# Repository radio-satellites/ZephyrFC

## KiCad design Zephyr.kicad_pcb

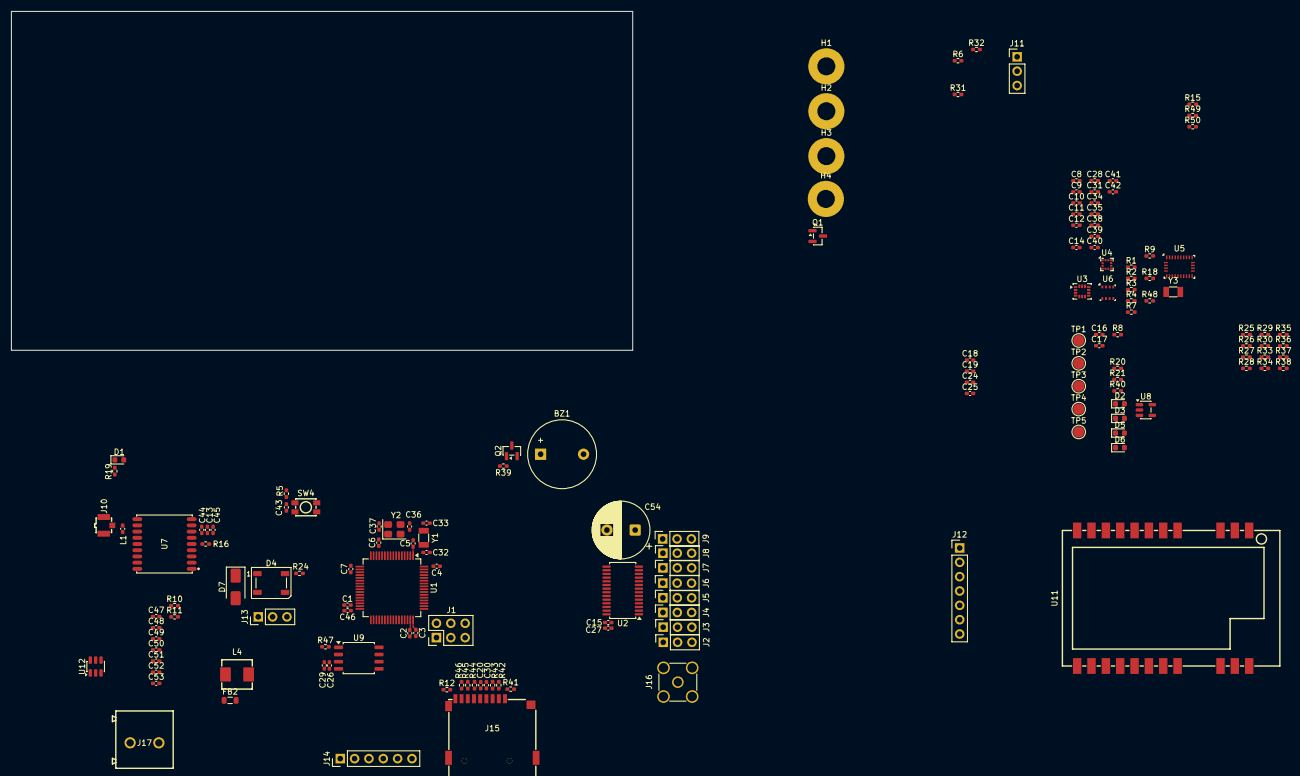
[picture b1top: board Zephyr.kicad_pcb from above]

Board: 2 copper layers, 110.0 x 60.0 mm, 150 parts (0 on the bottom side), 94 nets.

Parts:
BZ1: Buzzer; Buzzer_12x9.5RM7.6
C1, C2, C24, C27, C28, C30, C35, C39, C42, C45, C47: 10uF; C_0402_1005Metric_Pad0.74x0.62mm_HandSolder
C3, C4, C5, C6, C7, C12, C13, C14, C15, C19, C20, C25, C26, C31, C34, C38, C40, C41, C43, C44, C46, C48, C49: 100nF; C_0402_1005Metric_Pad0.74x0.62mm_HandSolder
C8, C9: 18pF; C_0402_1005Metric_Pad0.74x0.62mm_HandSolder
C10, C11, C18, C29: 1uF; C_0402_1005Metric_Pad0.74x0.62mm_HandSolder
C16, C17: 22uF; C_0402_1005Metric_Pad0.74x0.62mm_HandSolder
C32, C33: 15pF; C_0402_1005Metric_Pad0.74x0.62mm_HandSolder
C36, C37: 14pF; C_0402_1005Metric_Pad0.74x0.62mm_HandSolder
C50, C51: 47uF; C_0402_1005Metric_Pad0.74x0.62mm_HandSolder
C52: 75pF; C_0402_1005Metric_Pad0.74x0.62mm_HandSolder
C53: 1nF; C_0402_1005Metric_Pad0.74x0.62mm_HandSolder
C54: 470uF; CP_Radial_D10.0mm_P5.00mm
D1, D2, D3, D5, D6: LED; LED_0603_1608Metric
D4: WS2812B-B/T; LED_WS2812B_PLCC4_5.0x5.0mm_P3.2mm
D7: SS14; D_SMA
FB2: FerriteBead; L_0805_2012Metric
H1, H2, H3, H4: MountingHole_Pad; MountingHole_3.2mm_M3_Pad
J1: Conn_02x03_Counter_Clockwise; PinHeader_2x03_P2.54mm_Vertical
J2, J3, J4, J5, J6, J7, J8, J9: Conn_01x03; PinSocket_1x03_P2.54mm_Vertical
J10: Conn_Coaxial; RF-SMD_FRF05002-JSS103M
J11, J13: Conn_01x03; PinHeader_1x03_P2.54mm_Vertical
J12: Conn_01x07_Pin; PinHeader_1x07_P2.54mm_Vertical
J14: Conn_01x06; PinHeader_1x06_P2.54mm_Vertical
J15: Micro_SD_Card; TF-SMD_HX-TF-CARD-H1.8-SY
J16: Conn_Coaxial; SMA_Amphenol_901-144_Vertical
J17: Screw_Terminal_01x02; CONN-TH_2P-P5.00_WJ500V-5.08-2P
L1: 47nH; L_0402_1005Metric_Pad0.77x0.64mm_HandSolder
L4: 10uH; IND-SMD_L5.4-W5.2_MPCA-0518
Q1, Q2: MMBT3904; SOT-23
R1, R3, R5, R6, R7, R9, R12, R15, R16, R18, R32, R39, R41, R42, R43, R44, R45, R46, R47, R48: 10k; R_0402_1005Metric_Pad0.72x0.64mm_HandSolder
R2, R4: 2.2k; R_0402_1005Metric_Pad0.72x0.64mm_HandSolder
R8, R20, R21, R31, R40: 1k; R_0402_1005Metric_Pad0.72x0.64mm_HandSolder
R10: 100k; R_0402_1005Metric_Pad0.72x0.64mm_HandSolder
R11: 13.3k; R_0402_1005Metric_Pad0.72x0.64mm_HandSolder
R19: 470R; R_0402_1005Metric_Pad0.72x0.64mm_HandSolder
R24: 220R; R_0402_1005Metric_Pad0.72x0.64mm_HandSolder
R25, R28, R30, R34, R36, R38: 66k; R_0402_1005Metric_Pad0.72x0.64mm_HandSolder
R26, R27, R29, R33, R35, R37: 34k; R_0402_1005Metric_Pad0.72x0.64mm_HandSolder
R49, R50: 4.7k; R_0402_1005Metric_Pad0.72x0.64mm_HandSolder
SW4: SW_Push; SW-SMD_4P-L3.5-W3.0-P1.50-LS4.7
TP1, TP2, TP3, TP4, TP5: TestPoint; TestPoint_Pad_D2.0mm
U1: STM32F405RGT6; LQFP-64_10x10mm_P0.5mm
U2: PCA9685PW; TSSOP-28_4.4x9.7mm_P0.65mm
U3: LSM6DSOXTR; LGA-14_3x2.5mm_P0.5mm_LayoutBorder3x4y
U4: LIS3MDL; LGA-12_2x2mm_P0.5mm
U5: BNO055; LGA-28_5.2x3.8mm_P0.5mm
U6: BME280; Bosch_LGA-8_2.5x2.5mm_P0.65mm_ClockwisePinNumbering
U7: ATGM336H-5N31; GPSM-SMD_ATGM336H-TR
U8: TLV75733PDBVR; SOT-23-5
U9: W25Q128JVS; SOIC-8_5.3x5.3mm_P1.27mm
U11: E22-400M30S; WIRELM-SMD_E22-400M30S
U12: TPS54302; SOT-23-6
Y1, Y3: 32.768KHz 12.5pF; Crystal_SMD_3215-2Pin_3.2x1.5mm
Y2: 8MHz 12pF; Crystal_SMD_3225-4Pin_3.2x2.5mm

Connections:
+3.3V: C3.1, C4.1, C5.1, C6.1, C7.1, C12.1, C13.1, C14.1, C15.1, C17.1, C20.1, C26.1, C27.1, C28.1, C29.1, C30.1, C31.1, C34.1, C35.1, C38.1, C39.1, C40.1, C41.1, C42.1, C44.1, C45.1, C46.1, D3.2 (A), J1.6, J11.2, J14.3, J15.4 (VDD), R1.1, R2.1, R4.1, R5.1, R9.2, R12.1, R16.1, R18.1, R32.2, R41.1, R42.1, R43.1, R44.1, R45.1, R46.1, R47.1, R49.1, R50.1, TP2.1, U1.1 (VBAT), U1.13 (VDDA), U1.19 (VDD), U1.32 (VDD), U1.48 (VDD), U1.64 (VDD), U2.28 (VDD), U3.5 (VDDIO), U3.8 (VDD), U3.12 (CS), U4.5 (Vdd), U4.6 (Vdd_IO), U4.10 (~CS), U5.3 (VDD), U5.4 (~BOOT_LOAD_PIN), U5.28 (VDDIO), U6.6 (VDDIO), U6.8 (VDD), U7.6 (VBAT), U7.8 (VCC), U7.9 (NRESET), U8.5 (OUT), U9.3 (~WP/IO_{2}), U9.7 (~HOLD/~RESET/IO_{3}), U9.8 (VCC)
+5V: C16.1, C18.1, C19.1, C24.1, C25.1, D2.2 (A), D7.2 (A), FB2.2, J13.2, J14.2, Q2.3 (C), TP1.1, U8.1 (IN), U8.3 (EN), U11.9 (VCC), U11.10 (VCC)
+12V: C47.1, C48.1, D6.2 (A), J17.1, TP5.1, U12.3 (VIN)
/ADC/ADC_0: R25.1, R26.2, U1.25 (ADC1_IN15)
/ADC/ADC_1: R27.2, R28.1, U1.24 (ADC1_IN14)
/ADC/ADC_2: R29.2, R30.1, U1.11 (ADC1_IN13)
/ADC/ADC_3: R33.2, R34.1, U1.10 (ADC1_IN12)
/ADC/ADC_4: R35.2, R36.1, U1.9 (ADC1_IN11)
/ADC/ADC_5: R37.2, R38.1, U1.8 (ADC1_IN10)
/BUZZER: Q2.1 (B), R39.1, U1.26 (PB0)
/CD: J15.9 (CD), R12.2, U1.39 (PC8)
/CLK_FLASH: U1.34 (SPI2_SCK), U9.6 (CLK)
/CS_FLASH: R47.2, U1.33 (SPI2_NSS), U9.1 (~CS)
/DEBUG_RX: J14.4, U1.42 (USART1_TX)
/DEBUG_TX: J14.5, U1.43 (USART1_RX)
/Guidance Sensors/BNO_RESET: R1.2, U1.62 (PB9), U5.11 (~RESET)
/Guidance Sensors/SCL: R4.2, U1.30 (I2C2_SDA), U3.13 (SCL), U4.1 (SCL/SPC), U5.19 (COM1), U6.4 (SCK)
/Guidance Sensors/SDA: R2.2, U1.29 (I2C2_SCL), U3.14 (SDA), U4.11 (SDA/SDI/SDO), U5.20 (COM0), U6.3 (SDI)
/MISO_FLASH: U1.35 (SPI2_MISO), U9.2 (DO/IO_{1})
/MOSI_FLASH: U1.36 (SPI2_MOSI), U9.5 (DI/IO_{0})
/NEOPIXEL_OUT: R24.1, U1.27 (PB1)
/NRST: C43.1, J1.4, R5.2, SW4.2, U1.7 (NRST)
/RCC_OSC32_IN: C32.2, U1.3 (RCC_OSC32_IN), Y1.1
/RCC_OSC32_OUT: C33.2, U1.4 (RCC_OSC32_OUT), Y1.2
/RCC_OSC_IN: C36.2, U1.5 (RCC_OSC_IN), Y2.3
/RCC_OSC_OUT: C37.2, U1.6 (RCC_OSC_OUT), Y2.1
/Radio/RF_ANT: J16.1 (In), U11.21 (ANT)
/Radio/RF_MISO: U1.22 (SPI1_MISO), U11.16 (MISO)
/Radio/RF_MOSI: U1.23 (SPI1_MOSI), U11.17 (MOSI)
/Radio/RF_NSS: U1.20 (SPI1_NSS), U11.19 (NSS)
/Radio/RF_SCK: U1.21 (SPI1_SCK), U11.18 (SCK)
/SBUS_IN: J11.1, R31.1
/SBUS_RX: Q1.3 (C), R32.1, U1.54 (UART5_RX)
/SD_CS: J15.2 (DAT3/CD), R42.2, U1.40 (PC9)
/SD_MISO: J15.7 (DAT0), R45.2, U1.52 (SPI3_MISO)
/SD_MOSI: J15.3 (CMD), R43.2, U1.53 (SPI3_MOSI)
/SD_SCK: J15.5 (CLK), R44.2, U1.51 (SPI3_SCK)
/SYS_JTCK-SWCLK: J1.2, U1.49 (SYS_JTCK-SWCLK)
/SYS_JTDO-SWO: J1.3, U1.55 (SYS_JTDO-SWO)
/SYS_JTMS-SWDIO: J1.1, U1.46 (SYS_JTMS-SWDIO)
/Servo Driver/LED0: J2.1, U2.6 (LED0)
/Servo Driver/LED1: J3.1, U2.7 (LED1)
/Servo Driver/LED2: J4.1, U2.8 (LED2)
/Servo Driver/LED3: J5.1, U2.9 (LED3)
/Servo Driver/LED4: J6.1, U2.10 (LED4)
/Servo Driver/LED5: J7.1, U2.11 (LED5)
/Servo Driver/LED6: J8.1, U2.12 (LED6)
/Servo Driver/LED7: J9.1, U2.13 (LED7)
/Servo Driver/SERVO_SCL: R50.2, U1.58 (I2C1_SCL), U2.27 (SDA)
/Servo Driver/SERVO_SDA: R49.2, U1.59 (I2C1_SDA), U2.26 (SCL)
GND: BZ1.2 (-), C1.2, C2.2, C3.2, C4.2, C5.2, C6.2, C7.2, C8.2, C9.2, C10.2, C11.2, C12.2, C13.2, C14.2, C15.2, C16.2, C17.2, C18.2, C19.2, C20.2, C24.2, C25.2, C26.2, C27.2, C28.2, C29.2, C30.2, C31.2, C32.1, C33.1, C34.2, C35.2, C36.1, C37.1, C38.2, C39.2, C40.2, C41.2, C42.2, C43.2, C44.2, C45.2, C46.2, C47.2, C48.2, C50.2, C51.2, C53.2, C54.2, D4.3 (VSS), H1.1, H2.1, H3.1, H4.1, J1.5, J2.3, J3.3, J4.3, J5.3, J6.3, J7.3, J8.3, J9.3, J10.2 (Ext), J11.3, J12.7, J13.3, J14.6, J15.6 (VSS), J15.10 (SHIELD), J16.2 (Ext), J17.2, Q1.2 (E), R3.2, R6.2, R7.2, R8.2, R11.2, R15.1, R19.1, R20.2, R21.2, R25.2, R28.2, R30.2, R34.2, R36.2, R38.2, R39.2, R40.2, R48.2, SW4.1, TP3.1, U1.12 (VSSA), U1.18 (VSS), U1.63 (VSS), U2.1 (A0), U2.2 (A1), U2.3 (A2), U2.4 (A3), U2.5 (A4), U2.14 (VSS), U2.24 (A5), U3.6 (GND), U3.7 (GND), U4.2 (GND), U4.3 (GND), U4.12 (GND), U5.2 (GND), U5.5 (PS1), U5.6 (PS0), U5.18 (COM2), U5.25 (GNDIO), U6.1 (GND), U6.7 (GND), U7.1 (GND), U7.10 (GND), U7.12 (GND), U8.2 (GND), U9.4 (GND), U11.1 (GND), U11.2 (GND), U11.3 (GND), U11.4 (GND), U11.5 (GND), U11.11 (GND), U11.12 (GND), U11.20 (GND), U11.22 (GND), U12.1 (GND), Y2.2, Y2.4
unnamed: BZ1.1 (+), Q2.2 (E)
unnamed: C50.1, C51.1, C52.1, FB2.1, L4.2, R10.1
unnamed: D1.2 (A), U7.4 (1PPS)
unnamed: D1.1 (K), R19.2
unnamed: D2.1 (K), R20.1
unnamed: D3.1 (K), R21.1
unnamed: D4.4 (DIN), R24.2
unnamed: D4.2 (DOUT), J13.1
unnamed: D4.1 (VDD), D7.1 (K)
unnamed: D5.1 (K), R40.1
unnamed: D6.1 (K), R8.1
unnamed: J10.1 (In), L1.2, U7.11 (RF_IN)
unnamed: J12.1, R37.1
unnamed: J12.2, R35.1
unnamed: J12.3, R33.1
unnamed: J12.4, R29.1
unnamed: J12.5, R27.1
unnamed: J12.6, R26.1
unnamed: J15.8 (DAT1), R46.2
unnamed: J15.1 (DAT2), R41.2
unnamed: Q1.1 (B), R31.2
unnamed: R6.1, U1.60 (BOOT0)
unnamed: C1.1, U1.31 (VCAP_1)
unnamed: C2.1, U1.47 (VCAP_2)
unnamed: R15.2, U2.23 (~OE)
unnamed: R48.1, U3.1 (SDO/SA0)
unnamed: C11.1, U4.4 (C1)
unnamed: R7.1, U4.9 (SDO/SA1)
unnamed: C10.1, U5.9 (CAP)
unnamed: R3.1, U5.17 (COM3)
unnamed: C8.1, U5.27 (XIN32), Y3.1
unnamed: C9.1, U5.26 (XOUT32), Y3.2
unnamed: R18.2, U6.2 (CSB)
unnamed: R9.1, U6.5 (SDO)
unnamed: R16.2, U7.5 (ON/OFF)
unnamed: L1.1, U7.14 (VCC_RF)
unnamed: C49.1, U12.6 (BOOT)
unnamed: C53.1, U12.5 (EN)
unnamed: C52.2, R10.2, R11.1, U12.4 (FB)
unnamed: C49.2, L4.1, U12.2 (SW)
RX_GPS: U1.14 (UART4_TX), U7.3 (RXD)
TX_GPS: U1.15 (UART4_RX), U7.2 (TXD)
VBUS: C54.1, D5.2 (A), J2.2, J3.2, J4.2, J5.2, J6.2, J7.2, J8.2, J9.2, J14.1, TP4.1

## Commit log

2026-01-25 Start ADC work
2026-01-27 Continue work on power supply
2026-01-27 4.2V Regulator design
2026-01-27 Work more on power
2026-01-28 Work on power supply...
2026-01-30 Add SD card
2026-01-30 GPS Bias tee upgrade
2026-01-30 Radio work
2026-01-30 SD card
2026-02-04 More work... SD, flash, etc.
2026-02-05 Start routing the microcontroller
2026-02-05 Initial routing
2026-02-07 Add more footprints!
2026-02-09 More schematic work
2026-02-09 Reset circuit fix (oops...)
2026-02-09 Do a few reroutes
2026-02-09 more routing
2026-02-14 Power redesign
2026-03-09 Continue work
2026-03-09 Start PCB layout
2026-03-12 Start layout
